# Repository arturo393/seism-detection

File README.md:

# Sistema de Detección de Sismos

Un sistema de detección de terremotos basado en acelerómetros que utiliza algoritmos avanzados de procesamiento de señales para detectar eventos sísmicos en tiempo real.

## 📋 Descripción

Este proyecto implementa un sistema completo de detección sísmica que procesa datos de acelerómetros utilizando parámetros como IQR (Rango Intercuartílico), CAV (Vector Acelerativo Acumulativo), RSL (Relación de Señal) y ZC (Cruces por Cero) para identificar eventos sísmicos.

### Características principales

- **Detección en tiempo real** de eventos sísmicos
- **Múltiples plataformas**: ESP8266 (v1) y Particle Photon (v2)
- **Soporte para múltiples acelerómetros**
- **Conectividad WiFi** para envío de datos
- **Georeferenciación** automática de eventos
- **Análisis de datos** con herramientas Python
- **Configuración remota** de parámetros

## 🏗️ Arquitectura del Sistema

### Versión 1 (ESP8266)
- **Microcontrolador**: NodeMCU 1.0 (ESP8266)
- **Ubicación**: `/prosismic/`
- **Acelerómetros soportados**:
  - SparkFun Triple Axis Accelerometer Breakout - MMA8452Q
  - MinIMU-9 v2 (L3GD20 y LSM303DLHC)
  - SparkFun Triple Axis Accelerometer Breakout - ADXL345
  - Módulo GY-291 ADXL345

### Versión 2 (Particle Photon)
- **Microcontrolador**: Particle Photon
- **Ubicación**: `/q_up/`
- **Acelerómetro**: MinIMU-V5 con LIS3MDL
- **Mejoras**: Configuración remota, mejor conectividad

## 🛠️ Instalación y Configuración

### Prerrequisitos

#### Para Versión 1 (ESP8266)
- Arduino IDE con soporte ESP8266
- Librerías necesarias (ver sección de dependencias)

#### Para Versión 2 (Particle Photon)
- Particle CLI o Particle Web IDE
- Cuenta en Particle Cloud

### Instalación de Dependencias

#### Versión 1 (ESP8266)
```bash
# Instalar soporte ESP8266 en Arduino IDE
# Agregar URL en Preferences: https://github.com/esp8266/Arduino
```

**Librerías requeridas:**
- [Arduino Time Library](https://github.com/PaulStoffregen/Time)
- [ArduinoSort](https://github.com/emilv/ArduinoSort)
- [ArduinoJson](https://github.com/bblanchon/ArduinoJson)
- [WiFi Location](https://github.com/gmag11/ESPWifiLocation)
- [WiFiManager](https://github.com/tzapu/WiFiManager)
- [LSM303 Arduino Library](https://github.com/pololu/lsm303-arduino)
- [SparkFun MMA8452Q Library](https://github.com/sparkfun/SparkFun_MMA8452Q_Arduino_Library)
- [Arduino-ADXL345](https://github.com/jarzebski/Arduino-ADXL345)

#### Versión 2 (Particle Photon)
```bash
# Instalar Particle CLI
npm install -g particle-cli
particle login
```

### Configuración

1. **Configurar WiFi** (Versión 1):
   ```cpp
   #define _SSID "tu_red_wifi"
   #define _NETPASS "tu_contraseña"
   ```

2. **Configurar parámetros de detección**:
   ```cpp
   #define SAMPLES 200           // Número de muestras
   #define Factor_IQR  5.0      // Factor de referencia IQR
   #define Factor_CAV  1.5      // Factor de referencia CAV
   #define Factor_ZC   1        // Factor de referencia ZC
   ```

### Compilación y Carga

#### Versión 1 (ESP8266)
```bash
cd prosismic/prosismic/
# Abrir prosismic.ino en Arduino IDE
# Seleccionar board: NodeMCU 1.0 (ESP-12E Module)
# Compilar y cargar
```

#### Versión 2 (Particle Photon)
```bash
cd q_up/
particle compile photon
particle flash [device_name] firmware.bin
```

## 🚀 Uso

### Parámetros de Detección

El sistema utiliza los siguientes parámetros para detectar eventos sísmicos:

- **IQR (Interquartile Range)**: Mide la variabilidad de la señal
- **CAV (Cumulative Absolute Velocity)**: Acumulación de velocidad absoluta
- **RSL (Response Spectrum Level)**: Nivel del espectro de respuesta
- **ZC (Zero Crossings)**: Cruces por cero de la señal

### Salida de Datos

El sistema genera datos en formato serie con el siguiente formato:
```
Date Time(hh:mm:ss:mss) Sample x y z NetAcc xMax yMax zMax NetAccMax t_NetAccMax ZC IQR CAV RSL

22/6/2017 21:22:36.673    68 0 -2 -2 282  3 6 3 6 608 673 26 103 200 111
22/6/2017 21:22:36.684    69 0 -1 -2 223  2 6 3 6 608 684 25 103 199 111
```

### Herramientas de Análisis

#### Visualización de datos (Python)
```bash
python acc_plot.py
```

#### Servidor serie para captura de datos
```bash
python serial_server.py
```

## 📁 Estructura del Proyecto

```
seism-detection/
├── prosismic/           # Versión 1 (ESP8266)
│   ├── prosismic/
│   │   └── prosismic.ino
│   ├── lib/             # Librerías específicas
│   └── platformio.ini
├── q_up/                # Versión 2 (Particle Photon)
│   ├── src/
│   │   └── q_up.ino
│   ├── lib/             # Librerías específicas
│   └── project.properties
├── Case/                # Diseños de carcasa (DXF)
├── Hardware/            # Esquemas electrónicos
├── acc_plot.py          # Herramienta de visualización
├── serial_server.py     # Servidor de captura de datos
└── README.md
```

## 🔧 Configuración Avanzada

### Parámetros Configurables

- `FrecRPS`: Frecuencia de muestreo (Hz)
- `SAMPLES`: Número de muestras para análisis
- `DPTIME`: Tiempo para determinar desplazamiento (ms)
- `MTIME`: Tiempo para determinar movimiento (ms)

### API de Configuración Remota (Versión 2)

La versión 2 permite configuración remota a través de Particle Cloud:
- `setIQR(value)`: Configurar umbral IQR
- `setCAV(value)`: Configurar umbral CAV
- `setRSL(value)`: Configurar umbral RSL
- `setRestartTime(time)`: Configurar tiempo de reinicio

## 🤝 Contribución

¡Las contribuciones son bienvenidas! Por favor lee [CONTRIBUTING.md](CONTRIBUTING.md) para detalles sobre el proceso de contribución.

## 📄 Licencia

Este proyecto está licenciado bajo la Licencia MIT - ver el archivo [LICENSE](LICENSE) para detalles.

## 👨‍💻 Autor

**Arturo Veras** - *Desarrollo inicial* - [arturo393](https://github.com/arturo393)

## 📖 Documentación Adicional

Para más información detallada sobre el funcionamiento del algoritmo, revisar la [Wiki del proyecto](https://github.com/arturo393/seism-detection/wiki).

## 🏷️ Versiones

Ver [CHANGELOG.md](CHANGELOG.md) para una lista de cambios en cada versión.

---

⚡ **Estado del Proyecto**: Activo y en desarrollo continuo

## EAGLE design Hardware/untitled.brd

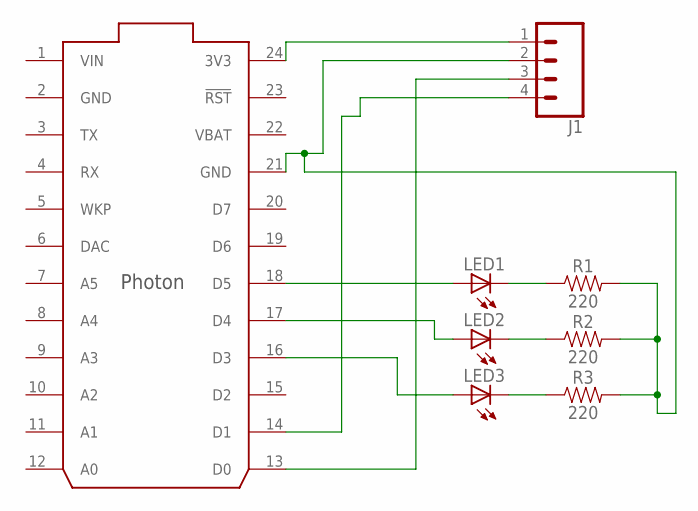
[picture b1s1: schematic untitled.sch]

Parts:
J1: CONN_04; 1X04
LED1, LED2, LED3: LEDCHIP-LED0805; CHIP-LED0805
R1, R2, R3: 220; 0603
U$1: PHOTON_WITH_HEADERS; PHOTON

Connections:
GND: U$1.2 (GND)
unnamed: LED1.A, U$1.18 (D5)
unnamed: LED2.A, U$1.17 (D4)
unnamed: LED3.A, U$1.16 (D3)
unnamed: LED3.C, R3.1
unnamed: LED2.C, R2.1
unnamed: LED1.C, R1.1
unnamed: J1.3, U$1.13 (D0)
unnamed: J1.4, U$1.14 (D1)
unnamed: J1.1, U$1.24 (3V3)
unnamed: J1.2, R1.2, R2.2, R3.2, U$1.21 (GND)
VBAT: U$1.22 (VBAT)
VIN: U$1.1 (VIN)

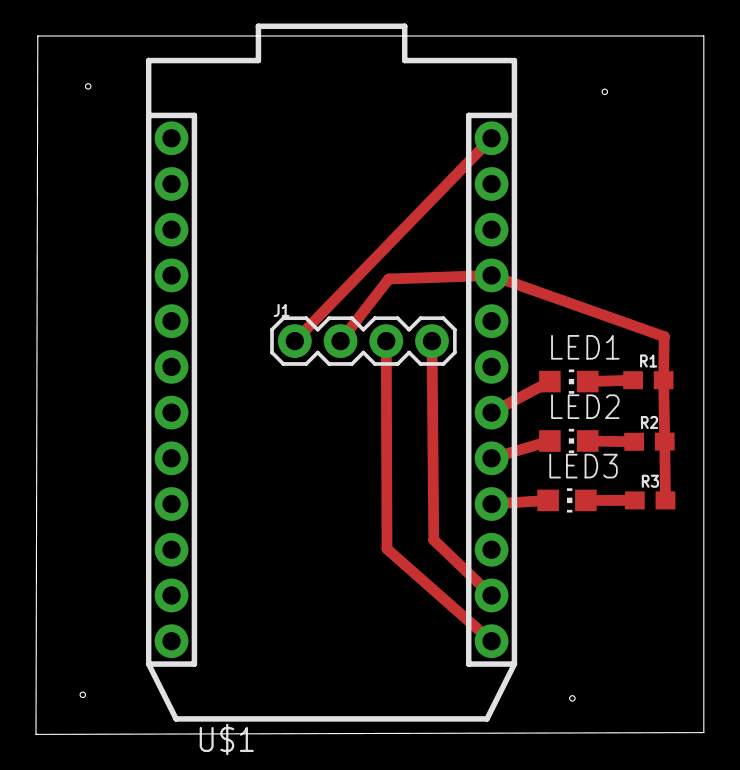
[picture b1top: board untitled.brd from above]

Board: 2 copper layers, 37.1 x 38.8 mm, 8 parts (0 on the bottom side), 10 nets.

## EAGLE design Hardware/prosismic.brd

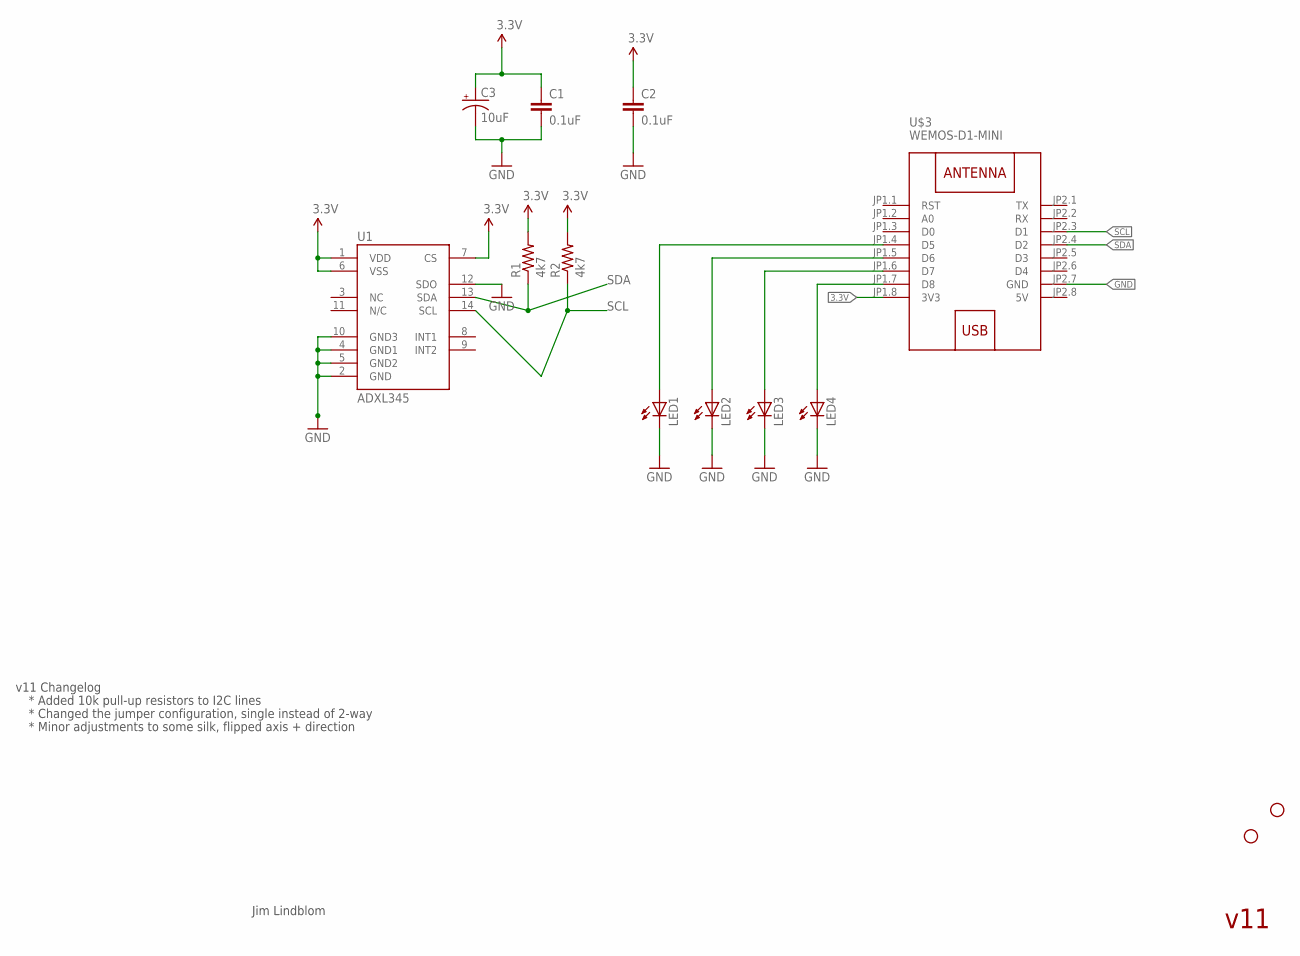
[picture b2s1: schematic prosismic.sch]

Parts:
C1, C2: 0.1uF; 0402-CAP
C3: 10uF; EIA3216
JP3, JP4: STAND-OFF
LED1, LED2, LED3, LED4: LED3MM
R1, R2: 4k7; 0402-RES
U1: ADXL345; LGA14
U$3: WEMOS-D1-MINI

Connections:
3.3V: C1.1, C2.1, C3.A (+), R1.2, R2.2, U1.1 (VDD), U1.6 (VSS), U1.7 (CS), U$3.JP1.8 (3V3)
5V: U$3.JP2.8 (5V)
D1: LED1.A, U$3.JP1.4 (D5)
D2: LED2.A, U$3.JP1.5 (D6)
D3: LED3.A, U$3.JP1.6 (D7)
D4: LED4.A, U$3.JP1.7 (D8)
GND: C1.2, C2.2, C3.C (-), LED1.K (C), LED2.K (C), LED3.K (C), LED4.K (C), U1.2 (GND), U1.4 (GND1), U1.5 (GND2), U1.10 (GND3), U1.12 (SDO), U$3.JP2.7 (GND)
SCL: R2.1, U1.14 (SCL), U$3.JP2.3 (D1)
SDA: R1.1, U1.13 (SDA), U$3.JP2.4 (D2)

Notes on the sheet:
Jim Lindblom
v11 Changelog
* Added 10k pull-up resistors to I2C lines
* Changed the jumper configuration, single instead of 2-way
* Minor adjustments to some silk, flipped axis + direction
v11

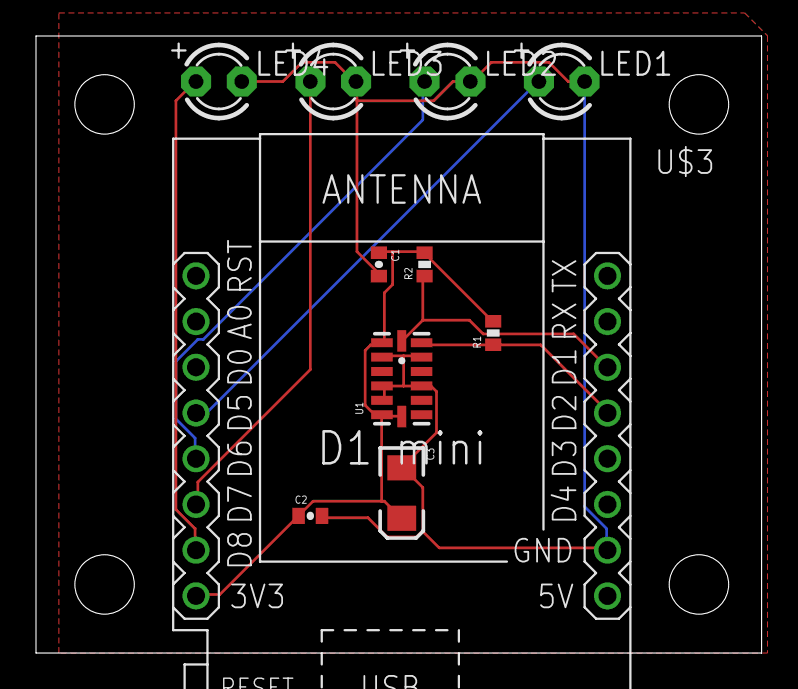
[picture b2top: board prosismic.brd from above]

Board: 2 copper layers, 40.3 x 34.3 mm, 15 parts (0 on the bottom side), 8 nets.

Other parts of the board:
JP1, JP2: STAND-OFF

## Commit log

2017-05-11 stable version. Have to upgrade the parameters. Check for IQR calculation
2017-05-11 first code
2017-05-12 fix some minor things
2017-05-12 no funciona
2017-05-19 Stable Version. Check the HP filter
2017-05-19 Stable version. Chek HP filter
2017-05-20 add ip geolocation. check the offset function
2017-05-26 Parameters calculation fixed. Check for offset function and reference calculation time
2017-06-03 LSM303DLH new algorith, check event trigger
2017-06-05 fixed detection algorithm
2017-06-05 ready algorithm. Missing recalculate parameters after x hours and fix geolocation
2017-06-08 fix geoip. Missing x hour parameter recalc
2017-06-08 code for save all data in Pc through serial port
2017-06-14 fix geo and RSL = 250
2017-06-16 fix ACNmax short to long. RSLref = 250 , add geo and remove RSL event trigger
2017-06-22 README.md
    First readme for uses, instrucctions and anything else.
2017-06-22 add offset recale, see TRNM for change the time. Add Wifi ssid configuration
2017-06-22 Add libraries requirements
2017-06-29 First hardware ever
2017-06-30 First Particle program
2017-07-03 fix libraries
2017-07-03 time fixed ... still missing time sync with Partcile Cloud
2017-07-05 first mixed code
2017-07-05 fix ntp
2017-07-12 first add
2017-07-21 fixed ZICR parameter
2017-07-27 stable version.
2017-07-27 stable version
2017-07-28 fixed datasend on starup. First stable version
2017-07-31 Plaformio files for atom ide
2017-07-31 first version of the enclosure
2017-08-04 add x-axis and parameters plotter
2017-08-04 fixed display data
2017-08-04 no se que decir
2017-08-07 add filter
2017-08-21 big case
2017-08-21 add filter library
2017-08-21 mejoras
2017-08-21 minor fixes
2017-08-21 add status led display
2017-08-22 led update
2017-08-28 new version
2017-08-28 add new status server. finish version 3 case
2017-08-30 agregue versión 4
2017-08-31 version 1 complete
2017-08-31 Update README.md
    Agregué más datos al wishlist
2017-08-31 agregé cambie el nombre de la pagina del servidor web y una arreglé las luces del comienzo.
2017-09-01 Set theme jekyll-theme-hacker
2017-09-07 se arregla el aviso de estado
2017-09-07 nuevas tapas
2017-10-06 respaldo
2017-10-06 CAbios
2017-10-31 agregue librerias
2017-10-31 modificacion de librerias
2017-10-31 para dejar fuera archivos de eagle
2017-10-31 arreglo de librerias
2017-10-31 librerias modificadas
2017-10-31 librerias modificadas necesarias
2017-10-31 libreria modificada
2017-10-31 codigo inncesario
2017-11-06 actualizacion del codigo particle
2017-11-06 no subir los archivos log
2017-11-06 agregue wire.h para que funciora la libreria del acelerometro
2017-11-09 revisar la conexión al servidor
2017-11-12 actualizacion de prosismic
2017-11-13 tiempo del servidor arregaldo
2017-11-14 listo la modificación de variables y conexión con el server
2017-11-15 arreglo de Google maps
2017-11-16 ya no es necesario
2017-11-17 agregué libreria Filter y organicé funciones
2025-08-27 Initial plan
2025-08-27 Create comprehensive documentation (README, CONTRIBUTING, LICENSE, CHANGELOG)
2025-08-27 Complete repository documentation and cleanup

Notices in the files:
parts and their libraries:
diy-modules: Released under the Creative Commons Attribution 4.0 International License: http://creativecommons.org/licenses/by/4.0
SparkFun-Connectors: Licensing: Creative Commons ShareAlike 4.0 International - https://creativecommons.org/licenses/by-sa/4.0
